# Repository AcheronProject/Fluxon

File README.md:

# Acheron 40-SM-S-STM32-MX-TH-WI (Codename "Fluxon")

See [this page](https://gondolindrim.github.io/AcheronDocs/fluxon/intro.html) for the Fluxon PCB documentation (still not written yet as of june of 2020).

## Introduction

The Fluxon is a replacement PCB for the Vortex Core keyboard. It supports the default layouts of the Vortex Core, with a 1.75-2.75 split spacebar. The PCB also supports two extra bottom row layouts: one with a 6.25 spacebar one and other with a 7 unit spacebar. See the picture below for details. 

The PCB is powered by a STM32L072CxTx and is QMK compatible.

The indicator LEDs of the stock PCB were substituted by SK6812 (WS2812-compatible controller-integrated seriallized RGB LEDs) which can be configured as per the QMK capabilities.

## Supported layouts

Click [this link](http://www.keyboard-layout-editor.com/#/gists/73be427d3e8086a9253feece2dae6974) for the KLE file for the Fluxon.

## Renders

## Logo

The FLUXON logo was designed using the Deceptibots font by [Iconian Fonts](http://www.iconian.com/index.html). It was licensed for commercial use for this particular project through a donation. The FLUXON logo is therefore intellectual and commercial property of Álvaro "Gondolindrim" Volpato; the Deceptibots font is property of Iconian Fonts and their owners.

## Copyright notice

This project is released under the Acheron Open-Hardware License V1.2. For the license, please refer to the LICENCE.md file.

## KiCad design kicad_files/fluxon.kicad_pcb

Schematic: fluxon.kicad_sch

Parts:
C1, C2, C3: 100n; C_0805_2012Metric_Pad1.15x1.40mm_HandSolder
C4: 4.7nF; C_0805_2012Metric
C5, C6: 1u; CP_EIA-3216-10_Kemet-I_Pad1.58x1.35mm_HandSolder
C7: 4.7n; C_0805_2012Metric_Pad1.15x1.40mm_HandSolder
C8: 10u; C_0805_2012Metric_Pad1.15x1.40mm_HandSolder
C9, C10, C11, C15: 100n; C_0402_1005Metric
C12, C16: 4.7u; C_0402_1005Metric
C13: 1u; C_0402_1005Metric
C14: 10n; C_0402_1005Metric
C17: 1u; C_0805_2012Metric_Pad1.15x1.40mm_HandSolder
D1, D2, D3, D4, D5, D6, D7, D8, D9, D10, D11, D12, D13, D14, D15, D16, D17, D18, D19, D20, D21, D22, D23, D24, D25, D26, D27, D28, D29, D30, D31, D32, D33, D34, D35, D36, D37, D38, D39, D40, D41, D42, D43, D44, D45, D46, D47, D53: 1N4148W; D_SOD-123
D48, D49, D50: SK6812MINI-E; SK6812MINI_3535_6028_3.2x2.8mm_Round; MPN SK812MINI-E
D51: RB060M-60TR; D_SOD-123; Manufacturer Part Number RB060M-60TR; LCSC Part Number C114257
D52: SMF6.0A; D_SOD-123; Manufacturer Part Number SMF6.0A; LCSC Part Number C123790
F1: SL1210150; Fuse_1210_3225Metric; Manufacturer Part Number SL1210150; LCSC Part Number C70175
GR1: OSHLogo; osh-logo
GR2: Fluxon Plated Logo; fluxon_logo
GR3: Acheron Logo; acheronLong
GR4: Fluxon Big Logo; fluxon_logo_220x56.8mm
GR5, GR6, GR7: Warning Sign; warning_sign_3.6x3.2mm
J1: ARM SWD; Conn_ARM_JTAG_SWD_6
J2: U-F-M5DD-W-2; Korean-Hroparts_ U-F-M5DD-W-2; Manufacturer Part Number U-F-M5DD-W-2; LCSC Part Number C145793
J3: Conn_02x10; PinHeader_2x8_P2.54mm_Vertical
Q1: BSS138; SOT-23; Manufacturer Part Number BSS138; LCSC Part Number C193019
Q2: MUN5335DW1T1G; SOT-363_SC-70-6; Manufacturer Part Number MUN5335DW1T1G; LCSC Part Number C99680
R1, R2, R3: 3R; R_SMD_1206
R4, R6: 1k; R_SMD_1206
R5: 510R; R_SMD_1206
R7: 1M; R_SMD_1206
R8, R9, R13: 100k; R_SMD_1206
R10: 100R; R_SMD_1206
R11: 100; R_SMD_1206
R12: 33k; R_SMD_1206
S1: SW_Push; K2-1187SQ-A4SW-06; Manufacturer Part Number K2-1187SQ-A4SW-06; LCSC Part Number C92584
SW1: ESC; MX100
SW2: Q; MX100
SW3: W; MX100
SW4: E; MX100
SW5: R; MX100
SW6: T; MX100
SW7: Y; MX100
SW8: U; MX100
SW9: I; MX100
SW10: O; MX100
SW11: P; MX100
SW12: DEL; MX100
SW13: TAB_125; MX125
SW14: A; MX100
SW15: S; MX100
SW16: D; MX100
SW17: F; MX100
SW18: G; MX100
SW19: H; MX100
SW20: J; MX100
SW21: K; MX100
SW22: L; MX100
SW23: QUOTE; MX100
SW24: ENTER_175; MX175
SW25: LSHIFT_175; MX175
SW26: Z; MX100
SW27: X; MX100
SW28: C; MX100
SW29: V; MX100
SW30: B; MX100
SW31: N; MX100
SW32: M; MX100
SW33: COMMA; MX100
SW34: DOT; MX100
SW35: (D) RSHIFT_125; MX125
SW36: (D) FN_100; MX100
SW37: (F) RSHIFT_225; MX225
SW38: (I) RSHIFT_125; MX125
SW39: (I) SLASH_100; MX100
SW40: LCTRL_125; MX125
SW41: SUPER_100; MX100
SW42: LALT_100; MX100
SW43: SPC_625; MX625R
SW44: RALT_125; MX125
SW45: RGUI_100; MX100
SW46: RCTRL_125; MX125
SW47: BKSP; MX100
SW48: BKSP_2U; MX200
SW49: PN_100; MX100
SW50: SPC_175; MX175
SW51: SPC_275; MX275R
SW52: FN_100; MX100
SW53: RALT_100; MX100
SW54: LCTRL_150; MX150
SW55: LALT_150; MX150
SW56: SPC_700; MX700R
SW57: RCTRL_150; MX150
SW58: RALT_150; MX150
U1: USBLC6-2SC6; SOT-23-6; Manufacturer Part Number USBLC6-2SC6; LCSC Part Number C7519
U2: MCP1700-3302E/TT; SOT-23; Manufacturer Part Number MCP1700-3302E/TT; LCSC Part Number C39051
U3: STM32L072CBT6; LQFP-48_7x7mm_P0.5mm; Manufacturer Part Number STM32F072CBT6; LCSC Part Number C465977

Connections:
3.3V: C6.1, C9.2, C10.1, C11.2, C12.2, C13.2, C14.2, C15.2, C16.2, D51.2 (A), J1.1, J3.15, Q2.4 (C), R9.2, S1.1, U2.2 (VO), U3.1 (VBAT), U3.9 (VDDA), U3.24 (VDD), U3.36 (VDDIO2), U3.48 (VDD)
5V: C5.1, D51.1 (K), D52.1 (K), F1.1, R1.2, R2.1, R3.2, R4.2, R5.2, R8.2, U2.3 (VI)
/SHIELD: C4.2, J2.6 (Shield), R7.1
BOOT0: C8.2, R11.2, R12.1, R13.2, U3.44 (BOOT0)
Col1: SW1.1 (Col), SW13.1 (Col), SW25.1 (Col), SW40.1 (Col), SW54.1 (Col), U3.25 (PB12)
Col2: SW2.2 (Row), SW14.2 (Row), SW26.1 (Col), SW41.1 (Col), U3.11 (PA1/ADC_IN1)
Col3: SW3.1 (Col), SW15.1 (Col), SW27.1 (Col), SW42.1 (Col), SW55.1 (Col), U3.10 (PA0/ADC_IN0)
Col4: SW4.1 (Col), SW16.1 (Col), SW28.1 (Col), SW49.1 (Col), U3.6 (PF1/OSC_OUT)
Col5: SW5.1 (Col), SW17.1 (Col), SW29.1 (Col), SW50.1 (Col), U3.5 (PF0/OSC_IN)
Col6: SW6.1 (Col), SW18.1 (Col), SW30.1 (Col), SW43.1 (Col), SW51.1 (Col), SW56.1 (Col), U3.4 (PC15/OSC32_OUT)
Col7: SW7.1 (Col), SW19.1 (Col), SW31.1 (Col), U3.3 (PC14/OSC32_IN)
Col8: SW8.1 (Col), SW20.1 (Col), SW32.1 (Col), SW52.1 (Col), U3.2 (PC13)
Col9: SW9.1 (Col), SW21.1 (Col), SW33.1 (Col), SW44.1 (Col), SW53.1 (Col), SW57.1 (Col), U3.46 (SPI2_NSS/I2S2_WS/I2C1_SDA/TIM17_CH1/PB9)
Col10: SW10.1 (Col), SW22.1 (Col), SW34.1 (Col), SW45.1 (Col), U3.45 (I2C1_SCL/TIM16_CH1/PB8)
Col11: SW11.1 (Col), SW23.1 (Col), SW35.1 (Col), SW37.1 (Col), SW39.1 (Col), SW46.1 (Col), SW58.1 (Col), U3.43 (2C1_SDA/PB7)
Col12: SW12.1 (Col), SW24.1 (Col), SW36.1 (Col), SW38.1 (Col), SW47.2 (Row), SW48.2 (Row), U3.41 (SPI1_MOSI/I2S1_SD/TIM3_CH2/PB5)
D+: U1.6 (I/O1), U3.33 (USB_DP/PA12)
D-: U1.4 (I/O2), U3.32 (USB_DM/TIM1_CH4/PA11)
DBus+: J2.3 (D+), U1.1 (I/O1)
DBus-: J2.2 (D-), U1.3 (I/O2)
EXTRA3: J3.1, U3.30 (TIM1_CH2/PA9)
EXTRA5: J3.3, U3.29 (TIM1_CH1/PA8)
EXTRA6: J3.2, U3.31 (TIM1_CH3/PA10)
EXTRA8: J3.4, U3.27 (SPI2_MISO/I2S2_MCK/I2C2_SDA/TIM15_CH1/P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)
EXTRA9: J3.5, U3.22 (PB11/TIM2_CH4/I2C2_SDA)
EXTRA10: J3.6, U3.21 (PB10/SPI2_SCK/I2C2_SCL/TIM2_CH3)
EXTRA11: J3.7, U3.20 (PB2)
EXTRA12: J3.8, U3.19 (PB1/TIM3_CH4/TIM14_CH1/ADC_IN9)
EXTRA13: J3.9, U3.18 (PB0/TIM3_CH3/ADC_IN8)
EXTRA14: J3.10, U3.17 (PA7/TIM3_CH2/TIM14_CH1/ADC_IN7)
EXTRA15: J3.11, U3.16 (PA6/ADC_IN6/TIM3_CH1/TIM16_CH1)
EXTRA16: J3.12, U3.15 (PA5/ADC_IN5/DAC_OUT2)
EXTRA17: J3.13, U3.14 (PA4/TIM14_CH1/ADC_IN4)
EXTRA18: J3.14, U3.13 (PA3/TIM15_CH2/ADC_IN3)
GND: C1.1, C2.1, C3.1, C4.1, C5.2, C6.2, C7.2, C8.1, C9.1, C10.2, C11.1, C12.1, C13.1, C14.1, C15.1, C16.1, C17.1, D48.3 (VSS), D49.3 (VSS), D50.3 (VSS), D52.2 (A), J1.5, J2.5 (GND), J3.16, Q2.1 (C), R6.1, R7.2, R8.1, R9.1, R13.1, U1.2 (GND), U2.1 (GND), U3.8 (VSSA), U3.23 (VSS), U3.35 (VSS), U3.47 (VSS)
NRST: C7.1, J1.3, R10.2, U3.7 (NRST)
unnamed: C1.2, D48.1 (VDD), R1.1
unnamed: C2.2, D49.1 (VDD), R2.2
unnamed: C3.2, D50.1 (VDD), R3.1
unnamed: C17.2, Q1.1 (G), R5.1, R6.2
unnamed: D1.2 (A), SW1.2 (Row)
unnamed: D2.2 (A), SW2.1 (Col)
unnamed: D3.2 (A), SW3.2 (Row)
unnamed: D4.2 (A), SW4.2 (Row)
unnamed: D5.2 (A), SW5.2 (Row)
unnamed: D6.2 (A), SW6.2 (Row)
unnamed: D7.2 (A), SW7.2 (Row)
unnamed: D8.2 (A), SW8.2 (Row)
unnamed: D9.2 (A), SW9.2 (Row)
unnamed: D10.2 (A), SW10.2 (Row)
unnamed: D11.2 (A), SW11.2 (Row)
unnamed: D12.2 (A), SW12.2 (Row)
unnamed: D13.2 (A), SW13.2 (Row)
unnamed: D14.2 (A), SW14.1 (Col)
unnamed: D15.2 (A), SW15.2 (Row)
unnamed: D16.2 (A), SW16.2 (Row)
unnamed: D17.2 (A), SW17.2 (Row)
unnamed: D18.2 (A), SW18.2 (Row)
unnamed: D19.2 (A), SW19.2 (Row)
unnamed: D20.2 (A), SW20.2 (Row)
unnamed: D21.2 (A), SW21.2 (Row)
unnamed: D22.2 (A), SW22.2 (Row)
unnamed: D23.2 (A), SW23.2 (Row)
unnamed: D24.2 (A), SW24.2 (Row)
unnamed: D25.2 (A), SW25.2 (Row)
unnamed: D26.2 (A), SW26.2 (Row)
unnamed: D27.2 (A), SW27.2 (Row)
unnamed: D28.2 (A), SW28.2 (Row)
unnamed: D29.2 (A), SW29.2 (Row)
unnamed: D30.2 (A), SW30.2 (Row)
unnamed: D31.2 (A), SW31.2 (Row)
unnamed: D32.2 (A), SW32.2 (Row)
unnamed: D33.2 (A), SW33.2 (Row)
unnamed: D34.2 (A), SW34.2 (Row)
unnamed: D35.2 (A), SW35.2 (Row), SW37.2 (Row), SW39.2 (Row)
unnamed: D36.2 (A), SW36.2 (Row), SW38.2 (Row)
unnamed: D37.2 (A), SW40.2 (Row), SW54.2 (Row)
unnamed: D38.2 (A), SW41.2 (Row)
unnamed: D39.2 (A), SW42.2 (Row), SW55.2 (Row)
unnamed: D40.2 (A), SW43.2 (Row), SW51.2 (Row), SW56.2 (Row)
unnamed: D41.2 (A), SW44.2 (Row), SW53.2 (Row), SW57.2 (Row)
unnamed: D42.2 (A), SW45.2 (Row)
unnamed: D43.2 (A), SW46.2 (Row), SW58.2 (Row)
unnamed: D44.2 (A), SW47.1 (Col), SW48.1 (Col)
unnamed: D45.2 (A), SW49.2 (Row)
unnamed: D46.2 (A), SW50.2 (Row)
unnamed: D47.2 (A), SW52.2 (Row)
unnamed: D48.2 (DOUT), D49.4 (DIN)
unnamed: D49.2 (DOUT), D50.4 (DIN)
unnamed: D53.1 (K), R12.2
unnamed: D53.2 (A), Q2.2 (B), S1.2
unnamed: Q2.3 (C), R11.1
unnamed: Q2.6 (C), R10.1
RGB_3V3: Q1.2 (S), U3.28 (SPI2_MOSI/I2S2_SD/PB15)
RGB_5V: D48.4 (DIN), Q1.3 (D), R4.1
Row1: D1.1 (K), D2.1 (K), D3.1 (K), D4.1 (K), D5.1 (K), D6.1 (K), D7.1 (K), D8.1 (K), D9.1 (K), D10.1 (K), D11.1 (K), D12.1 (K), U3.38 (PA15)
Row2: D13.1 (K), D14.1 (K), D15.1 (K), D16.1 (K), D17.1 (K), D18.1 (K), D19.1 (K), D20.1 (K), D21.1 (K), D22.1 (K), D23.1 (K), D24.1 (K), U3.39 (SPI1_SCK/I2S1_CK/TIM2_CH2/PB3)
Row3: D25.1 (K), D26.1 (K), D27.1 (K), D28.1 (K), D29.1 (K), D30.1 (K), D31.1 (K), D32.1 (K), D33.1 (K), D34.1 (K), D35.1 (K), D36.1 (K), U3.12 (PA2/ADC_IN2)
Row4: D37.1 (K), D38.1 (K), D39.1 (K), D40.1 (K), D41.1 (K), D42.1 (K), D43.1 (K), D44.1 (K), D45.1 (K), D46.1 (K), D47.1 (K), U3.42 (I2C1_SCL/PB6)
SOFT_RESET: Q2.5 (B), U3.40 (SPI1_MISO/I2S1_MCK/TIM3_CH1/PB4)
SWCLK: J1.4, U3.37 (SWCLK/PA14)
SWDIO: J1.2, U3.34 (SWDIO/PA13)
VBUS: F1.2, J2.1 (VBUS), U1.5 (VBUS)

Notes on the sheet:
Shield
USB Connector
USD ESD
(D) Default bottom row
(T) Tsangan bottom row
(L) "Long" 6.25 bottom row
Serial programming
Power supply and protection circuit
Logos and flags
RGB indicators
Hard reset circuit
MCU
CBx are the bypass capacitors. Their value is specified in reference [2].

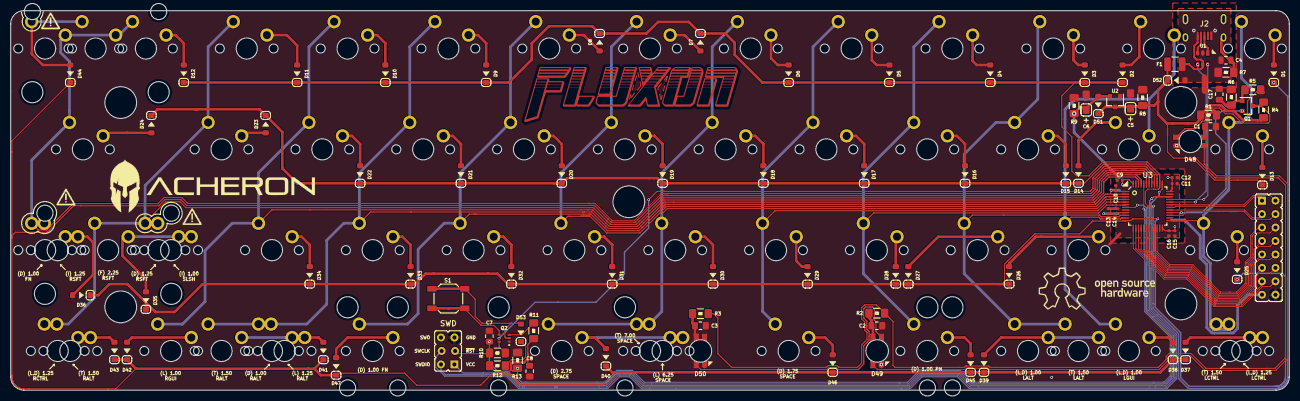
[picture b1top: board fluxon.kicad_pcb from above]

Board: 2 copper layers, 241.6 x 71.7 mm, 158 parts (1 on the bottom side), 103 nets.

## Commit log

2020-06-10 Add README and LICENSE
2020-06-11 Add software reset circuit
2020-06-11 Finish routing
2020-06-11 New renders and README
2020-06-11 Fix render link in README
2020-07-24 Quality of circuit improvements
    - Adoption of STM32L072 MCU variant
    - Changed TVS to SMF6.0A unidirectional
    - Addition of regulation capacitor to voltage divider resistors in the level shifter circuit
2020-07-24 Change LDO bypass capacitors to tantallum
2020-07-25 Change ARM SWD JTAG to 6 pin variant
2020-07-25 Silkscreen and tracing improvements
